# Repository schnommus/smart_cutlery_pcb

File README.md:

# Smart Cutlery (PCB)
ELEC3117 project, 2017S2. Jamon & Seb.

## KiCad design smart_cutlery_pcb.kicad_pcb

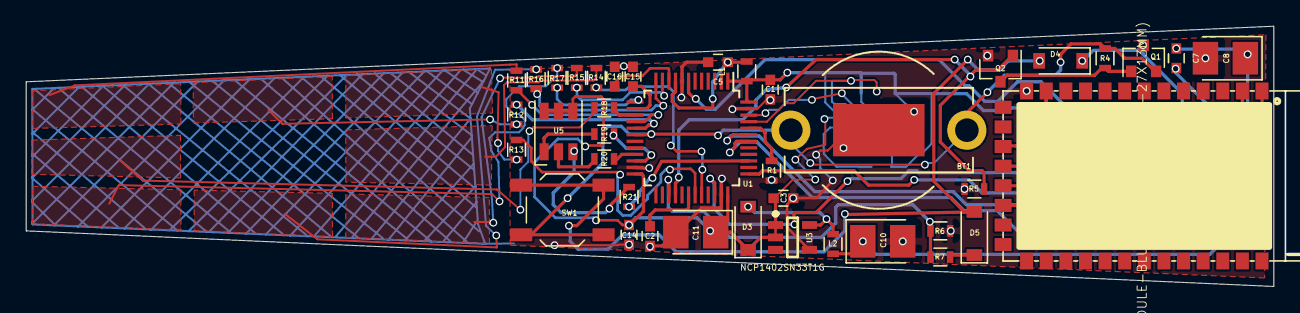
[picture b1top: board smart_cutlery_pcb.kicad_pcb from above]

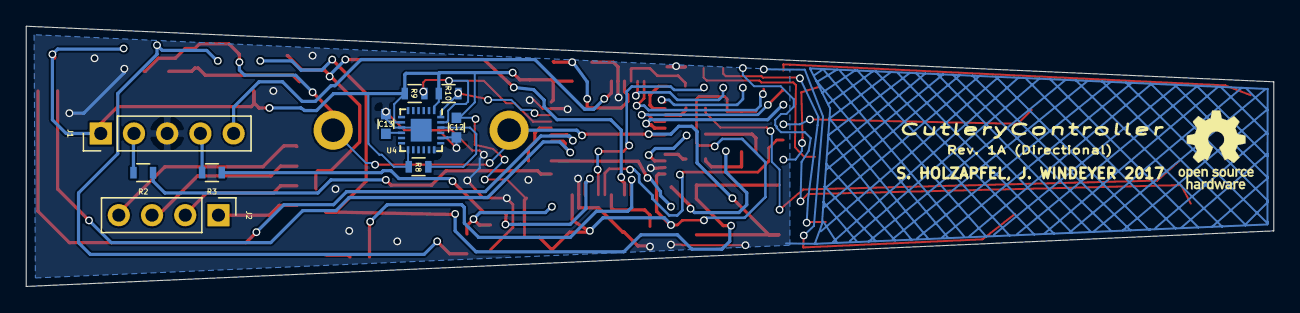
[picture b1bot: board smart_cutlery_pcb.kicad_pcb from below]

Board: 2 copper layers, 95.4 x 19.9 mm, 50 parts (10 on the bottom side), 44 nets.

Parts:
BT1: 3V CR1225; BC-2011-CR1225
C1, C2, C3, C5: 100n; C_0603
C7, C12, C13: 100nF; C_0603
C8: 100uF; CP_Tantalum_Case-B_EIA-3528-21_Reflow
C10: 10uF; CP_Tantalum_Case-B_EIA-3528-21_Reflow
C11: 68uF; CP_Tantalum_Case-B_EIA-3528-21_Reflow
C14, C15, C16: 47nF; C_0603
D3, D4, D5: MBR0520; D_SOD-123
J1: CONN_01X05; Pin_Header_Straight_1x05_Pitch2.54mm
J2: CONN_01X04; Pin_Header_Straight_1x04_Pitch2.54mm
L1: Ferrite; L_0603
L2: 47uH; L_0603
Q1: BSS84; SOT-23
Q2: BSS138; SOT-23
R1: 4.7k; R_0603
R2, R3: 100; R_0603
R4, R5: 100K; R_0603
R6: 4K7; R_0603
R7: 47K; R_0603
R8, R9, R10, R11, R12, R13, R14, R15, R16, R17, R18: 10K; R_0603
R19, R20, R21: 180; R_0603
SW1: TL3342; SW_SPST_TL3342
U1: STM32L053C6Tx; LQFP-48_7x7mm_Pitch0.5mm
U2: MODULE-BLUETOOTH-HC-05(34P-27X13MM); BT34P-SMD-1.5-26.9X13.0X2.2MM
U3: NCP1402SN33T1G; SOT95P275X110-5N
U4: MPU-9250; QFN-24-1EP_3x3mm_Pitch0.4mm
U5: ASMT-YTC2-0AA02; LED_RGB_PLCC-6

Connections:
+3V3: C1.1, C2.1, C3.1, C7.1, C8.1, C11.1, C12.1, D3.1, J1.1, L1.1, R8.1, R9.1, R10.1, U1.1, U1.24, U1.36, U1.48, U2.12, U3.1, U3.2, U4.1, U4.8, U4.13, U5.4, U5.5, U5.6
/ACCEL_GYRO_I2C_SCL: R9.2, U1.45, U4.23
/ACCEL_GYRO_I2C_SDA: R10.2, U1.46, U4.24
/BAT1_VSENSE: BT1.1, Q1.2, R4.2, SW1.1, U1.18
/BLUETOOTH_RX: U1.42, U2.2
/BLUETOOTH_TX: U1.43, U2.1
/LED_BLUE: R19.2, U1.22
/LED_GREEN: R20.2, U1.21
/LED_RED: R21.2, U1.39
/PWR_BUTTON: R6.1, R7.2, U1.27
/PWR_LATCH: Q2.1, R5.2, U1.28
/micro/SWD_CLK: R2.1, U1.37
/micro/SWD_IO: R3.1, U1.34
/micro/nRST: J1.5, U1.7
/touch_cap1: C16.2, U1.10
/touch_cap2: C15.2, U1.14
/touch_cap3: C14.2, U1.30
/touch_x1: R15.2, U1.11
/touch_x2: R16.2, U1.12
/touch_x3: R17.2, U1.13
/touch_x4: R18.2, U1.15
/touch_y1: R11.2, U1.16
/touch_y2: R12.2, U1.17
/touch_y3: R13.2, U1.31
/touch_y4: R14.2, U1.32
GND: BT1.2, C1.2, C2.2, C3.2, C5.2, C7.2, C8.2, C10.2, C11.2, C12.2, C13.2, C14.1, C15.1, C16.1, J1.3, Q2.2, R1.2, R5.1, R7.1, U1.8, U1.23, U1.35, U1.47, U2.13, U3.4, U4.9, U4.18, U4.20
unnamed: C5.1, L1.2, U1.9
unnamed: C10.1, D4.1, L2.1, Q1.3
unnamed: C13.1, U4.10
unnamed: D3.2, L2.2, U3.5
unnamed: D4.2, D5.2, SW1.2
unnamed: D5.1, R6.2
unnamed: J1.2, R2.2
unnamed: J1.4, R3.2
unnamed: J2.1, U2.19
unnamed: J2.2, U2.18
unnamed: J2.3, U2.17
unnamed: J2.4, U2.16
unnamed: Q1.1, Q2.3, R4.1
unnamed: R1.1, U1.44
unnamed: R8.2, U4.22
unnamed: R19.1, U5.1
unnamed: R20.1, U5.2
unnamed: R21.1, U5.3

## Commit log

2017-08-24 Added STM32L053 sub-schematic with debugging header etc
2017-08-24 Add bluetooth HC-05 module to schematic
2017-08-26 Add bluetooth module lib
2017-08-26 Capture boost converter, soft latching power
2017-08-26 Add accelerometer/gyro
2017-08-26 Add touch interface schematic
2017-08-26 Make top-level connections between microcontroller and everything else
2017-08-26 Add optional bubble around intertial sensor pcb
2017-09-01 Assigned some footprints and added CR1225 holder footprint
2017-09-01 Add switch footprints, add mode switch
2017-09-03 Update to new soft-latching power circuit
2017-09-04 Attempt layout
2017-09-04 attempt 1
2017-09-05 More changes, replace
2017-09-05 Do some routing
2017-09-06 More routing
2017-09-07 finish basic routing
2017-09-07 Place ref designators
2017-09-09 Finish touch pattern (rev1), ground hatching, gerbers r1
2017-09-09 Increase outline by 0.2mm on all sides to pass audit
2017-09-09 Finish pattern b, get fabbed
2017-09-13 Create relevant BOM links, export digikey BOM
2017-09-28 Add boost converter test results
2017-09-28 Update KiCAD version, add 150uH test, add text annotating component changes
2017-09-30 More inductor tests
2017-10-06 add efficiency readings for latest inductor
